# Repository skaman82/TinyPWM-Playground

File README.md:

# TinyPWM-Playground
PWM RC gadgets with the ATiny10

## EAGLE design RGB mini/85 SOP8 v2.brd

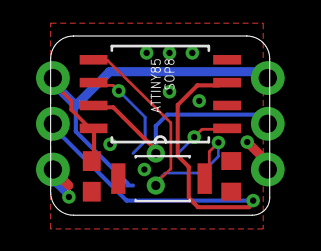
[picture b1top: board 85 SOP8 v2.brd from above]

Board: 2 copper layers, 12.2 x 10.0 mm, 7 parts (1 on the bottom side), 8 nets.

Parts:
C3: C0603
J1, J2: 1X03_NO_SILK
R1: R0603
S1: B3U-1000P; SW_B3U-1000P
U2: ATTINY85-15ST; SOIC127P798X216-8N
U$1: ISCP_PORTPOGONEW; ISCP_PADS_2ROW2HNEW

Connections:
5V: C3.1, J1.3, J2.3, U2.8, U$1.5V
GND: C3.2, J1.1, J2.1, S1.2, U2.4, U$1.GND
LED: J1.2, U2.3
MI: U2.6, U$1.MISO
MO: S1.1, U2.5, U$1.MO, U$1.MOSI
unnamed: R1.1, U2.7
RST: U2.1, U$1.RST
SCK: J2.2, R1.2, U$1.SC, U$1.SCK

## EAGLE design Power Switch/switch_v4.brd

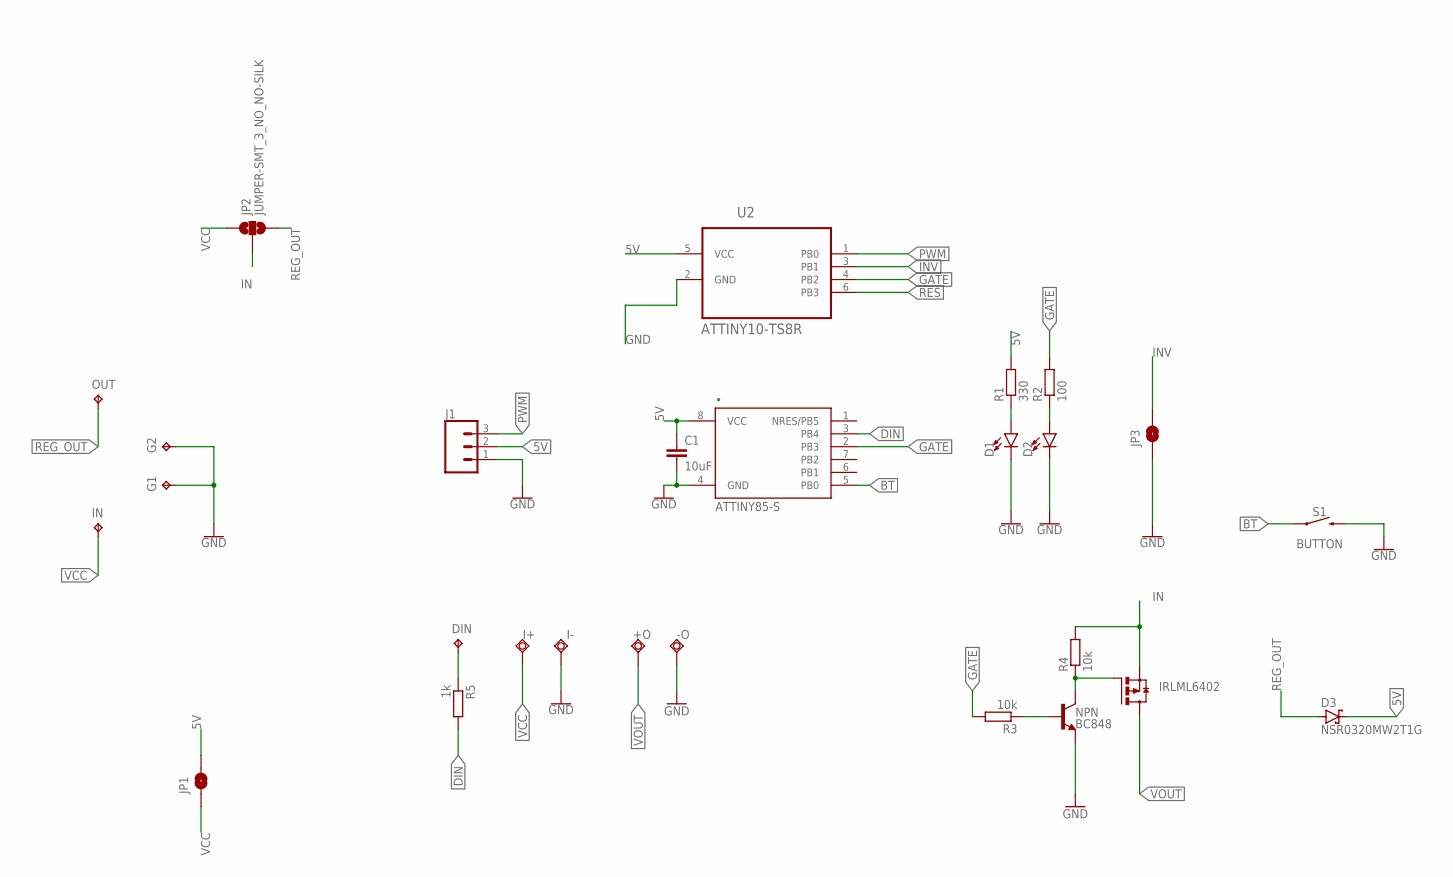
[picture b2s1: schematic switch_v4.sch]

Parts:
+O: TPSQTP20SQ; TP20SQ
-O: TPSQTP20SQ; TP20SQ
C1: 10uF; C0603K
D1, D2: LED0603; LED-0603
D3: NSR0320MW2T1G; SOD323_ST
DIN: TPTP15R; TP15R
G1, G2: TPTP15R; TP15R
I+: TPSQTP20SQ; TP20SQ
I-: TPSQTP20SQ; TP20SQ
IN: TPTP15R; TP15R
IRLML6402: FDN360P; SUPER-SOT3
J1: CONN_03; 1X03
JP1, JP3: JUMPER-SMT_2_NO_NO-SILK; SMT-JUMPER_2_NO_NO-SILK
JP2: JUMPER-SMT_3_NO_NO-SILK; SMT-JUMPER_3_NO_NO-SILK
NPN: BC848; SOT23-3
OUT: TPTP15R; TP15R
R1: 330; R0603
R2: 100; R0603
R3, R4: 10k; R0603
R5: 1k; R0603
S1: BUTTON; TACTILE_SWITCH_SMD_4.6X2.8MM
U2: ATTINY10-TS8R; SOT95P280X145-6N
•: ATTINY85-S; SOIC8_EIAJ_208MIL

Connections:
5V: C1.1, D3.C, J1.2, JP1.2, R1.2, U2.5 (VCC), •.8 (VCC)
BT: S1.1, S1.2 (1), •.5 (PB0)
DIN: R5.2, •.3 (PB4)
GATE: R2.2, R3.2, U2.4 (PB2), •.2 (PB3)
GND: -O.TP, C1.2, D1.C, D2.C, G1.TP, G2.TP, I-.TP, J1.1, JP3.1, NPN.2 (E), S1.3 (2), S1.4 (2), U2.2 (GND), •.4 (GND)
IN: IRLML6402.2 (S), JP2.2, R4.2
INV: JP3.2, U2.3 (PB1)
unnamed: NPN.1 (B), R3.1
unnamed: DIN.TP, R5.1
unnamed: D1.A, R1.1
unnamed: D2.A, R2.1
NN: IRLML6402.1 (G), NPN.3 (C), R4.1
PWM: J1.3, U2.1 (PB0)
REG_OUT: D3.A, JP2.3, OUT.TP
RES: U2.6 (PB3)
VCC: I+.TP, IN.TP, JP1.1, JP2.1
VOUT: +O.TP, IRLML6402.3 (D)

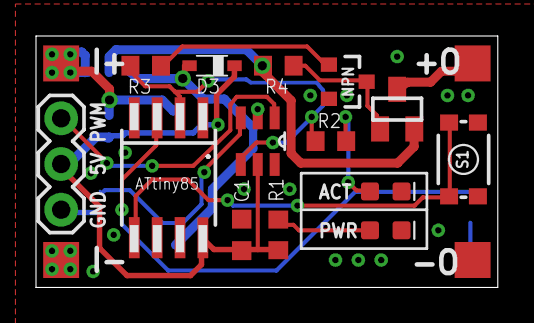
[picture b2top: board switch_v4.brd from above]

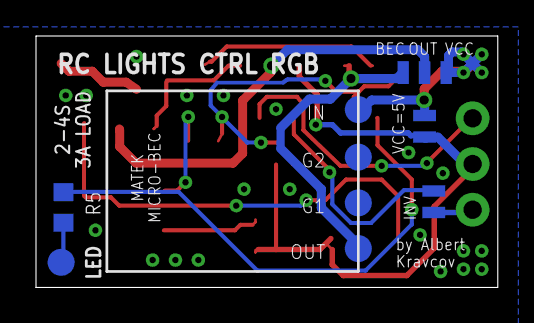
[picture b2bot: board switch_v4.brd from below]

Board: 2 copper layers, 25.7 x 14.0 mm, 27 parts (9 on the bottom side), 16 nets.

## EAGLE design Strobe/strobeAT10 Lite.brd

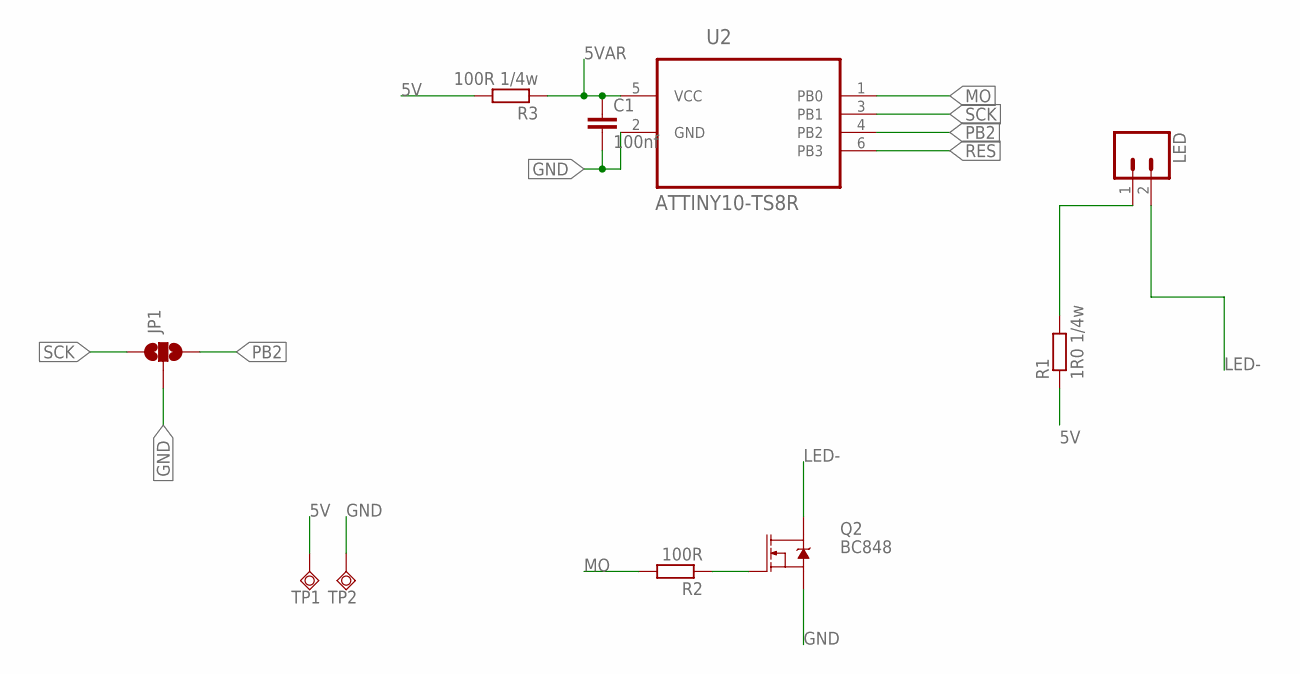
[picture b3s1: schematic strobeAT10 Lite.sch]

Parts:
C1: 100nf; C0603
JP1: JUMPER-SMT_3_NO_SILK; SMT-JUMPER_3_NO_SILK
LED: CONN_02PTH3; 1X02_LONGPADS
Q2: BC848; SOT23-3
R1: 1R0 1/4w; R0805
R2: 100R; R0603
R3: 100R 1/4w; R0805
TP1, TP2: TPSQPAD1-13Y; P1-13Y
U2: ATTINY10-TS8R; SOT95P280X145-6N

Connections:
5V: R1.1, R3.2, TP1.TP
5VAR: C1.1, R3.1, U2.5 (VCC)
GND: C1.2, JP1.2, Q2.2 (S), TP2.TP, U2.2 (GND)
LED-: LED.2, Q2.3 (D)
MO: R2.2, U2.1 (PB0)
unnamed: LED.1, R1.2
unnamed: Q2.1 (G), R2.1
PB2: JP1.3, U2.4 (PB2)
RES: U2.6 (PB3)
SCK: JP1.1, U2.3 (PB1)

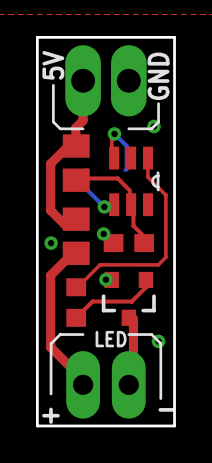
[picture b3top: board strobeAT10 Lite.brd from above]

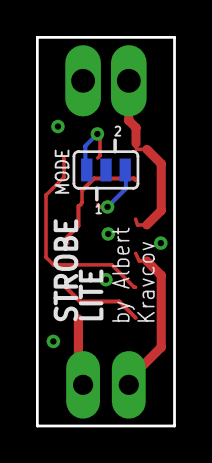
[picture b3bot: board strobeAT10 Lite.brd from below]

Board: 2 copper layers, 7.6 x 21.6 mm, 10 parts (3 on the bottom side), 9 nets.

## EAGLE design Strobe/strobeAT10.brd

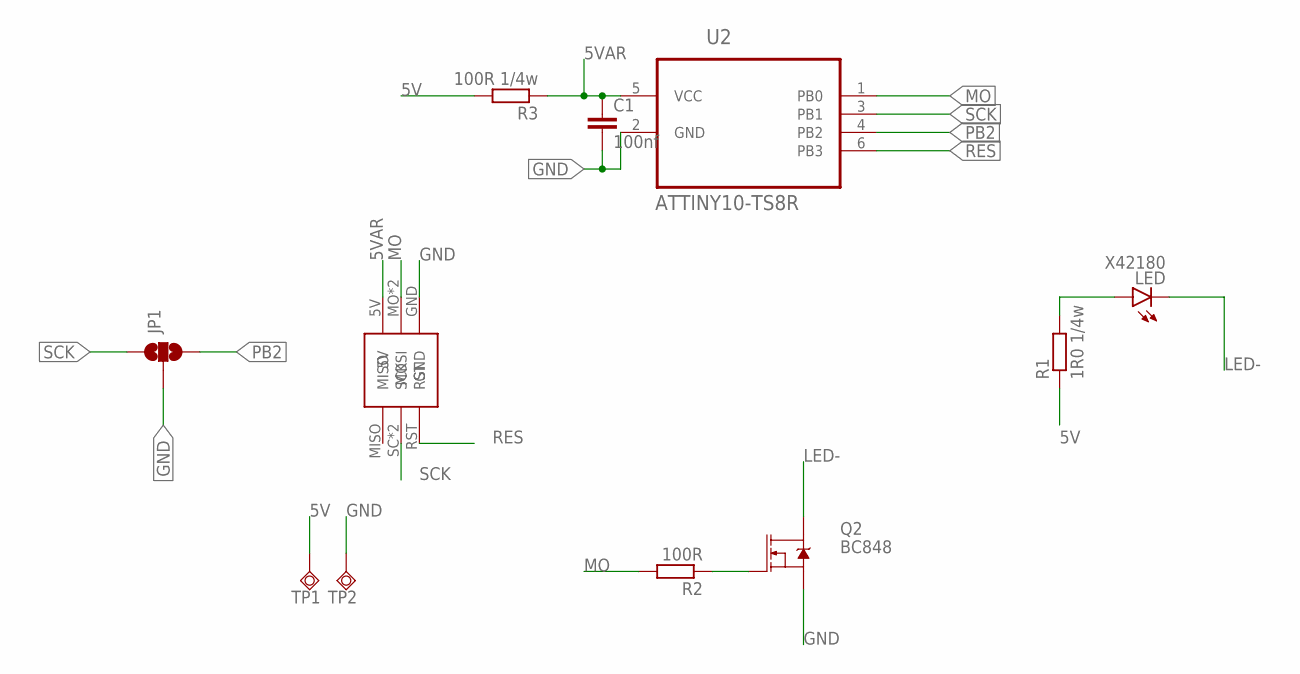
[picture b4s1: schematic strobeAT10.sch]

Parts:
C1: 100nf; C0603
JP1: JUMPER-SMT_3_NO_SILK; SMT-JUMPER_3_NO_SILK
LED: X42180; Z-POWER-LED-DOME-TYPE
Q2: BC848; SOT23-3
R1: 1R0 1/4w; R0805
R2: 100R; R0603
R3: 100R 1/4w; R0805
TP1, TP2: TPSQPAD1-13Y; P1-13Y
U2: ATTINY10-TS8R; SOT95P280X145-6N
U$1: ISCP_PORTPOGONEW; ISCP_PADS_2ROW2HNEW

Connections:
5V: R1.1, R3.2, TP1.TP
5VAR: C1.1, R3.1, U2.5 (VCC), U$1.5V
GND: C1.2, JP1.2, Q2.2 (S), TP2.TP, U2.2 (GND), U$1.GND
LED-: LED.C, Q2.3 (D)
MO: R2.2, U2.1 (PB0), U$1.MO (MOSI), U$1.MOSI
unnamed: LED.A, R1.2
unnamed: Q2.1 (G), R2.1
PB2: JP1.3, U2.4 (PB2)
RES: U2.6 (PB3), U$1.RST
SCK: JP1.1, U2.3 (PB1), U$1.SC (SCK), U$1.SCK

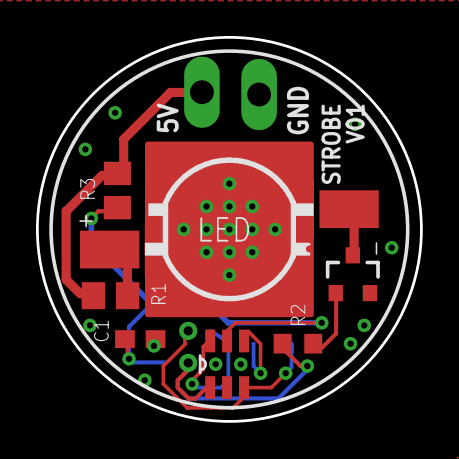
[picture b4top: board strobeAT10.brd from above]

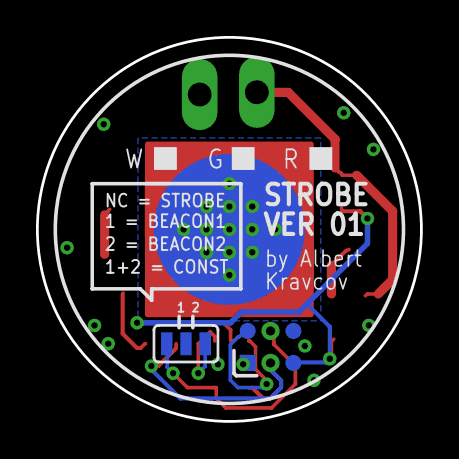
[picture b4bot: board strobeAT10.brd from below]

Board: 2 copper layers, 21.3 x 21.3 mm, 11 parts (4 on the bottom side), 10 nets.

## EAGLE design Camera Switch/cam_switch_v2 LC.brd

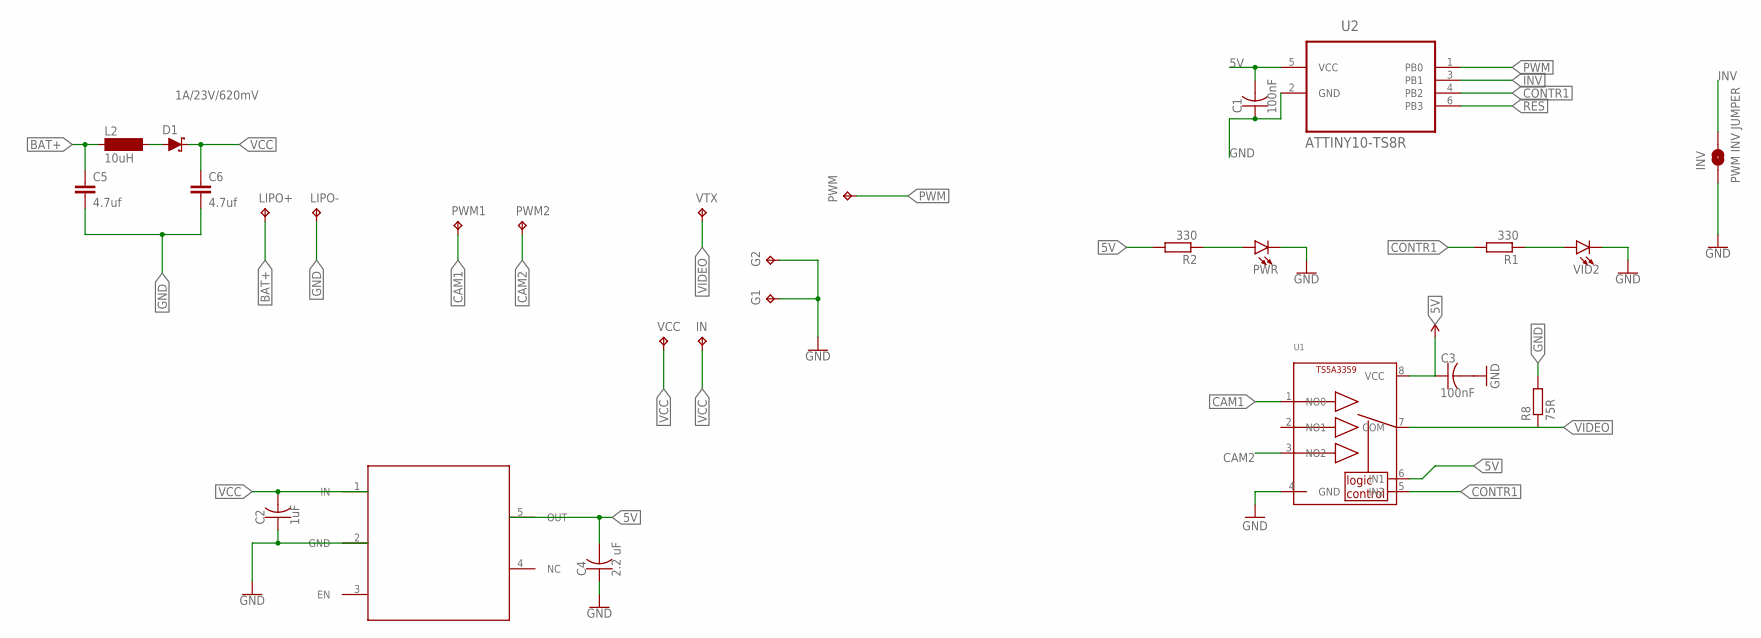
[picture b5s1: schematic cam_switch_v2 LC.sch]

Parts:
C1, C3: 100nF; C0603
C2: 1uF; C0805K
C4: 2.2 uF; C0603K
C5, C6: 4.7uf; C1206
D1: 1A/23V/620mV; SOD-323
G1, G2: TPTP20SQ; TP20SQ
IN: TPTP20SQ; TP20SQ
INV: PWM INV JUMPER; SMT-JUMPER_2_NO_NO-SILK
L2: 10uH; MS85_EDITED
LIPO+: TPTP20SQ; TP20SQ
LIPO-: TPTP20SQ; TP20SQ
PWM, PWM1, PWM2: TPTP20SQ; TP20SQ
PWR: LED0603; LED-0603
R1, R2: 330; R0603
R8: 75R; R0603
U1: TS5A3359; VFSOP-8
U2: ATTINY10-TS8R; SOT95P280X145-6N
U$1: TPS709; SOT95P280X145-5N
VCC: TPTP20SQ; TP20SQ
VID2: LED0603; LED-0603
VTX: TPTP20SQ; TP20SQ

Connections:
5V: C1.2, C3.1, C4.2, R2.2, U1.6 (IN1), U1.8 (VCC), U2.5 (VCC), U$1.5 (OUT)
BAT+: C5.1, L2.1, LIPO+.TP
CAM1: PWM1.TP, U1.1 (NO0)
CAM2: PWM2.TP, U1.3 (NO2)
CONTR1: R1.2, U1.5 (IN2), U2.4 (PB2)
GND: C1.1, C2.1, C3.2, C4.1, C5.2, C6.2, G1.TP, G2.TP, INV.1, LIPO-.TP, PWR.C, R8.2, U1.4 (GND), U2.2 (GND), U$1.2 (GND), VID2.C
INV: INV.2, U2.3 (PB1)
unnamed: R1.1, VID2.A
unnamed: PWR.A, R2.1
unnamed: D1.A, L2.2
PWM: PWM.TP, U2.1 (PB0)
RES: U2.6 (PB3)
VCC: C2.2, C6.1, D1.C, IN.TP, U$1.1 (IN), VCC.TP
VIDEO: R8.1, U1.7 (COM), VTX.TP

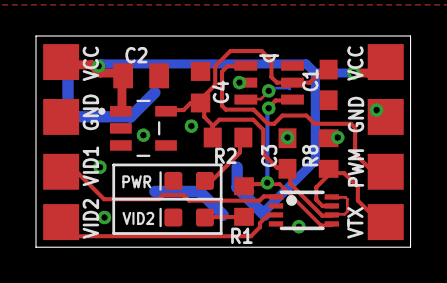
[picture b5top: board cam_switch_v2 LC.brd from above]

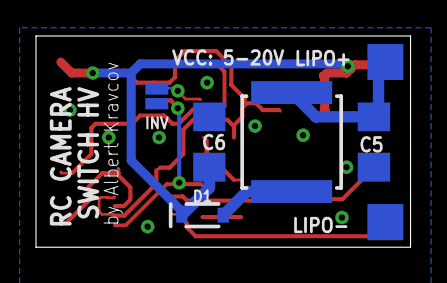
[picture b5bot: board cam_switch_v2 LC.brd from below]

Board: 2 copper layers, 20.8 x 11.7 mm, 27 parts (7 on the bottom side), 13 nets.

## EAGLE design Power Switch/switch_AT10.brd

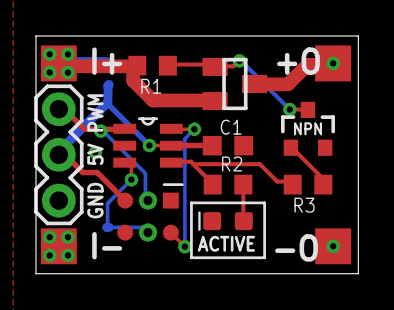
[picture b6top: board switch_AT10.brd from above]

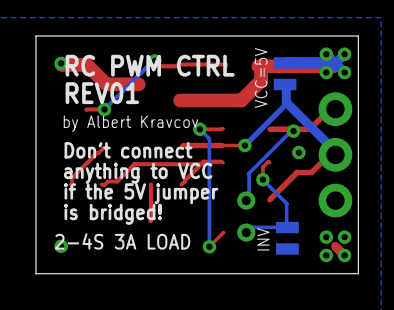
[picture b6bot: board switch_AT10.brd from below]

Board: 2 copper layers, 17.9 x 13.2 mm, 16 parts (2 on the bottom side), 11 nets.

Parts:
+O: TPSQTP20SQ; TP20SQ
-O: TPSQTP20SQ; TP20SQ
C1: 10uF; C0603K
D2: LED-0603
I+: TPSQTP20SQ; TP20SQ
I-: TPSQTP20SQ; TP20SQ
IRLML6402: FDN360P; SUPER-SOT3
J1: 1X03
JP1, JP2: JUMPER-SMT_2_NO_NO-SILK; SMT-JUMPER_2_NO_NO-SILK
NPN: BC848; SOT23-3
R1, R3: 10k; R0603
R2: 100; R0603
U2: ATTINY10-TS8R; SOT95P280X145-6N
U$2: ISCP_PORTPOGONEW; ISCP_PADS_2ROW2HNEW

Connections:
5V: C1.1, J1.2, JP1.2, U2.5, U$2.5V
GATE: R2.2, R3.2, U2.4
GND: -O.TP, C1.2, D2.C, I-.TP, J1.1, JP2.1, NPN.2, U2.2, U$2.GND
MO: J1.3, U2.1, U$2.MO, U$2.MOSI
unnamed: NPN.1, R3.1
unnamed: D2.A, R2.1
NN: IRLML6402.1, NPN.3, R1.1
RES: U2.6, U$2.RST
SCK: JP2.2, U2.3, U$2.SC, U$2.SCK
VCC: I+.TP, IRLML6402.2, JP1.1, R1.2
VOUT: +O.TP, IRLML6402.3

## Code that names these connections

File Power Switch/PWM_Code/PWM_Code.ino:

// RC PWM SWITCH
// By Albert Kravcov
//
// DIY ATTINY10 Hardware Package: https://github.com/sleemanj/optiboot/blob/master/dists/README.md#attiny

byte PWM_PIN = 0; //PB0 - PIN1
byte SENS_PIN = 1; //PB1 - PIN3
byte GATE_PIN = 2; //PB2 - PIN4


int pwm_value;

void setup() {

  pinMode(PWM_PIN, INPUT);
  pinMode(GATE_PIN, OUTPUT);
  pinMode(SENS_PIN, INPUT_PULLUP);

  digitalWrite(GATE_PIN, LOW);
}

void loop() {
  pwm_value = pulseIn(PWM_PIN, HIGH);

  if (digitalRead(SENS_PIN) == LOW) {

    if (pwm_value > 1700) {
      digitalWrite(GATE_PIN, HIGH);
    }
    else {
      digitalWrite(GATE_PIN, LOW);
    }
  }

  else if (digitalRead(SENS_PIN) != LOW) {

    if (pwm_value > 1300) {
      digitalWrite(GATE_PIN, HIGH);
    }
    else {
      digitalWrite(GATE_PIN, LOW);
    }
  }





}

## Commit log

2019-11-06 Create LICENSE
2019-11-06 File upload
2019-11-06 img update
2019-11-11 updated manual
2019-11-11 updated strobe code and cap values
2019-11-11 Alternative RGB code
2019-11-12 more rgb code work
2019-11-12 more code work
2019-11-12 bugfix
2019-11-12 styling
2019-11-12 cleanups
2019-11-13 strobe change
2019-11-13 manual work
2019-11-14 PCB updates (jumper distance) and a new RGB mini board
2019-11-14 Added Strobe Lite PCB
2019-11-15 RGB & PWM code update
2019-11-20 mini PCB update
2019-11-20 timing update
2020-06-12 jumper mode patch
2021-09-30 updated partslist
2023-03-20 gitignore

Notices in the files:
parts and their libraries:
SparkFun-LED: Licensing: Creative Commons ShareAlike 4.0 International - https://creativecommons.org/licenses/by-sa/4.0
